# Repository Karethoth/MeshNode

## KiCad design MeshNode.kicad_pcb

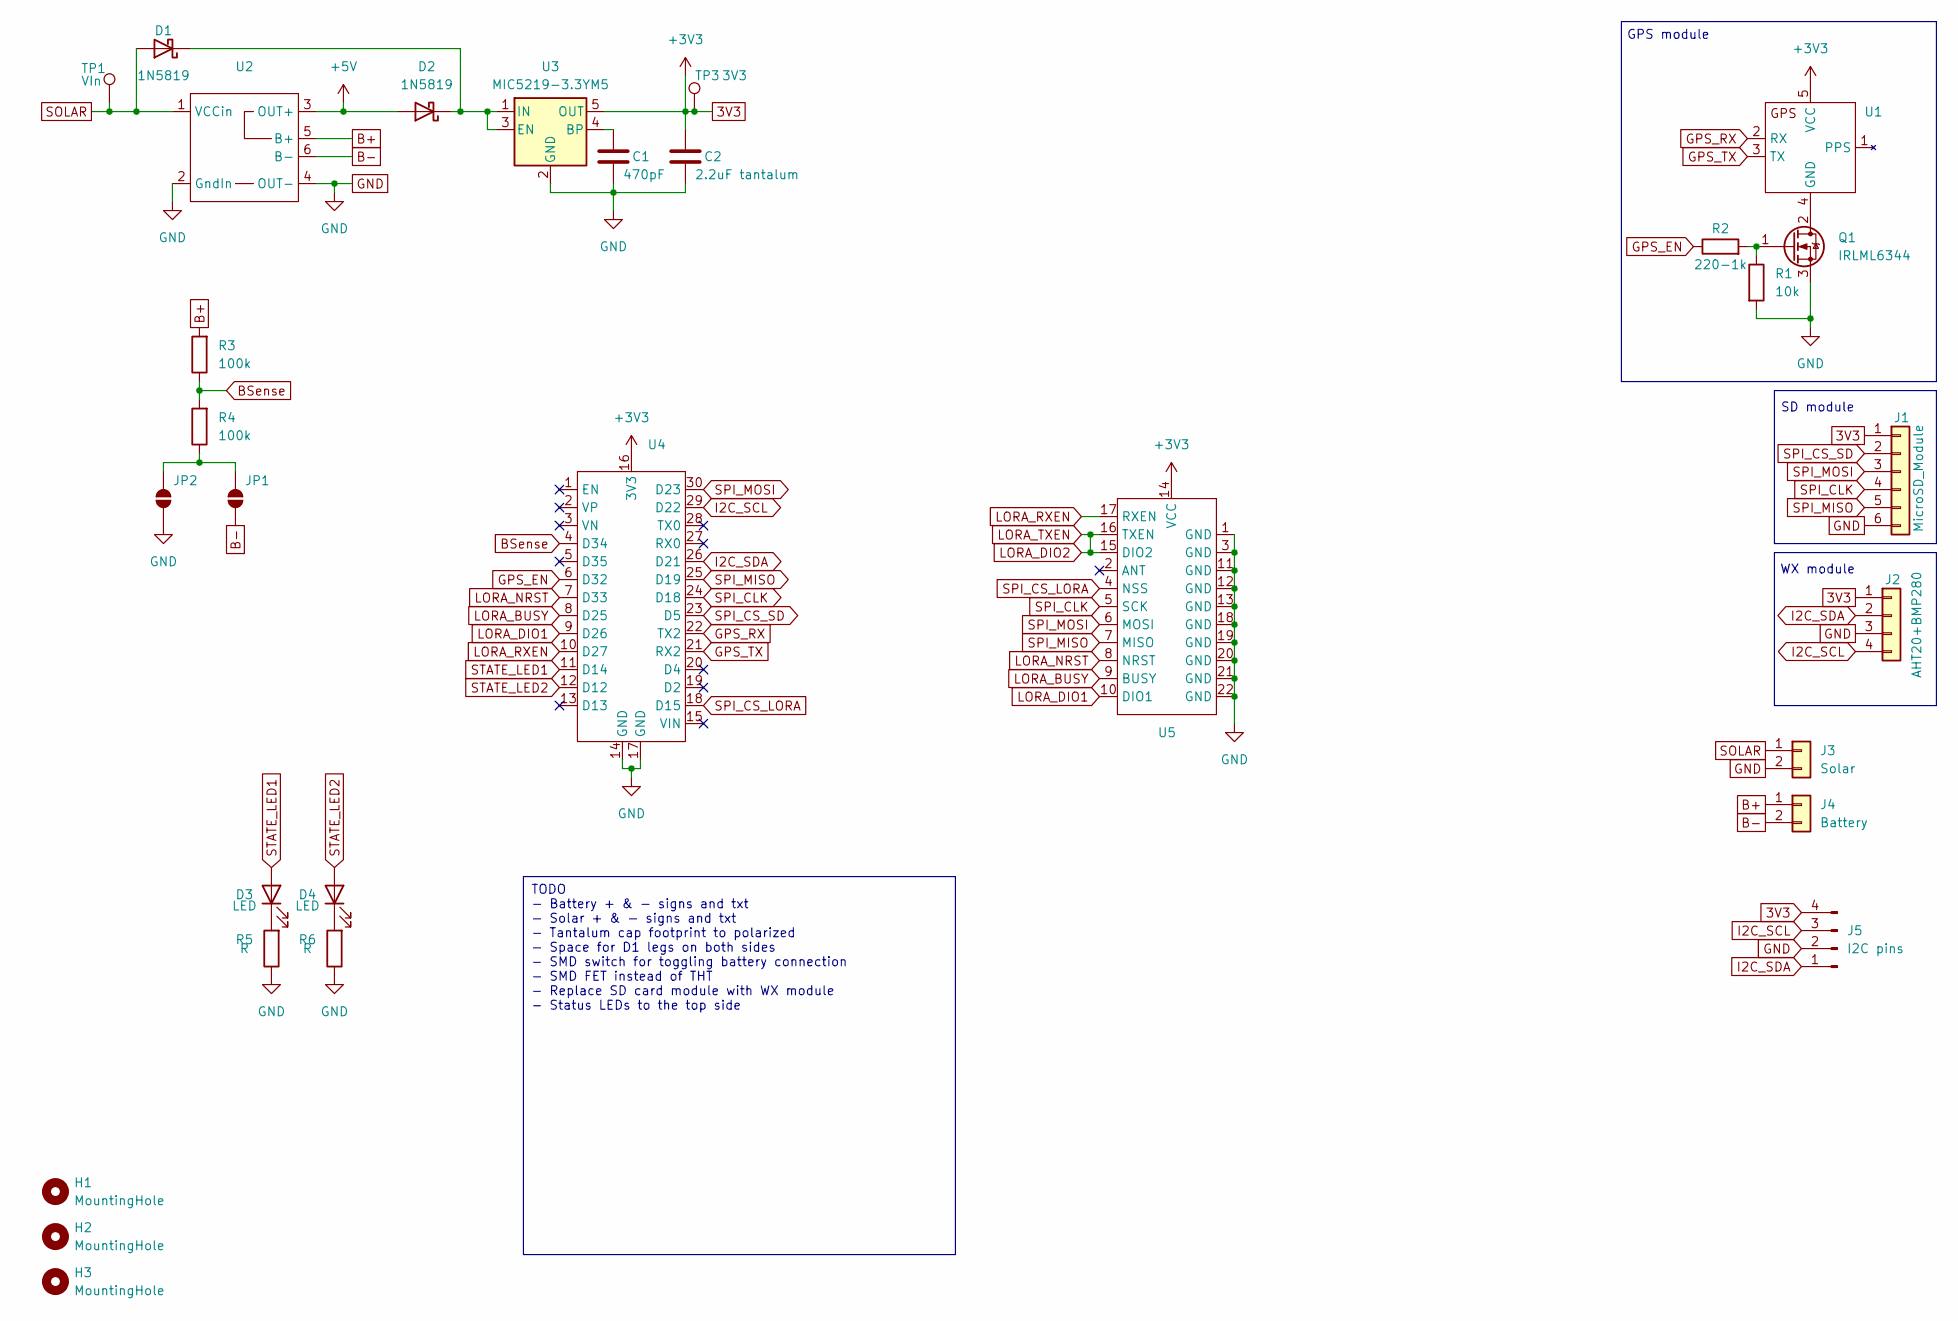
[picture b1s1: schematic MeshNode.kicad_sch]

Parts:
C1: 470pF; C_1206_3216Metric_Pad1.33x1.80mm_HandSolder
C2: 2.2uF tantalum; C_1206_3216Metric_Pad1.33x1.80mm_HandSolder
D1, D2: 1N5819; D_DO-41_SOD81_P10.16mm_Horizontal
D3, D4: LED; LED_0603_1608Metric_Pad1.05x0.95mm_HandSolder
H1, H2, H3: MountingHole; MountingHole_3mm
J1: MicroSD_Module
J2: AHT20+BMP280
J3: Solar; PinHeader_1x02_P2.54mm_Vertical
J4: Battery; PinHeader_1x02_P2.54mm_Vertical
J5: I2C pins; PinSocket_1x04_P2.54mm_Vertical
JP1, JP2: SolderJumper_2_Open; SolderJumper-2_P1.3mm_Open_RoundedPad1.0x1.5mm
Q1: IRLML6344; SOT-23
R1: 10k; R_0603_1608Metric
R2: 220-1k; R_0603_1608Metric
R3, R4: 100k; R_0603_1608Metric
R5, R6: R; R_0603_1608Metric_Pad0.98x0.95mm_HandSolder
TP1: VIn; TestPoint_Plated_Hole_D2.0mm
TP3: 3V3; TestPoint_Plated_Hole_D2.0mm
U1: GPS_Module
U2: TP4056
U3: MIC5219-3.3YM5; SOT-23-5
U4: WROOM32_Module
U5: EBYTE_900M22S

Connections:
3V3: C2.1, J1.1, J2.1, J5.4, TP3.1, U1.5 (VCC), U3.5 (OUT), U4.16 (3V3), U5.14 (VCC)
+5V: D2.2 (A), U2.3 (OUT+)
B+: J4.1, R3.2, U2.5 (B+)
B-: J4.2, JP1.2 (B), U2.6 (B-)
BSense: R3.1, R4.2, U4.4 (D34)
GND: C1.2, C2.2, J1.6, J2.3, J3.2, J5.2, JP2.1 (A), Q1.3 (S), R1.2, R5.1, R6.1, U2.2 (GndIn), U2.4 (OUT-), U3.2 (GND), U4.14 (GND), U4.17 (GND), U5.1 (GND), U5.3 (GND), U5.11 (GND), U5.12 (GND), U5.13 (GND), U5.18 (GND), U5.19 (GND), U5.20 (GND), U5.21 (GND), U5.22 (GND)
GPS_EN: R2.1, U4.6 (D32)
GPS_RX: U1.2 (RX), U4.22 (TX2)
GPS_TX: U1.3 (TX), U4.21 (RX2)
I2C_SCL: J2.4, J5.3, U4.29 (D22)
I2C_SDA: J2.2, J5.1, U4.26 (D21)
LORA_BUSY: U4.8 (D25), U5.9 (BUSY)
LORA_DIO1: U4.9 (D26), U5.10 (DIO1)
LORA_DIO2: U5.15 (DIO2), U5.16 (TXEN)
LORA_NRST: U4.7 (D33), U5.8 (NRST)
LORA_RXEN: U4.10 (D27), U5.17 (RXEN)
unnamed: D1.1 (K), D2.1 (K), U3.1 (IN), U3.3 (EN)
unnamed: D3.1 (K), R5.2
unnamed: D4.1 (K), R6.2
unnamed: JP1.1 (A), JP2.2 (B), R4.1
unnamed: Q1.2 (D), U1.4 (GND)
unnamed: Q1.1 (G), R1.1, R2.2
unnamed: C1.1, U3.4 (BP)
SOLAR: D1.2 (A), J3.1, TP1.1, U2.1 (VCCin)
SPI_CLK: J1.4, U4.24 (D18), U5.5 (SCK)
SPI_CS_LORA: U4.18 (D15), U5.4 (NSS)
SPI_CS_SD: J1.2, U4.23 (D5)
SPI_MISO: J1.5, U4.25 (D19), U5.7 (MISO)
SPI_MOSI: J1.3, U4.30 (D23), U5.6 (MOSI)
STATE_LED1: D3.2 (A), U4.11 (D14)
STATE_LED2: D4.2 (A), U4.12 (D12)

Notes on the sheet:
TODO - Battery + & - signs and txt - Solar + & - signs and txt - Tantalum cap footprint to polarized - Space for D1 legs on both sides - SMD switch for toggling battery connection - SMD FET instead of THT - Replace SD card module with WX module - Status LEDs to the top side
WX module
SD module
GPS module

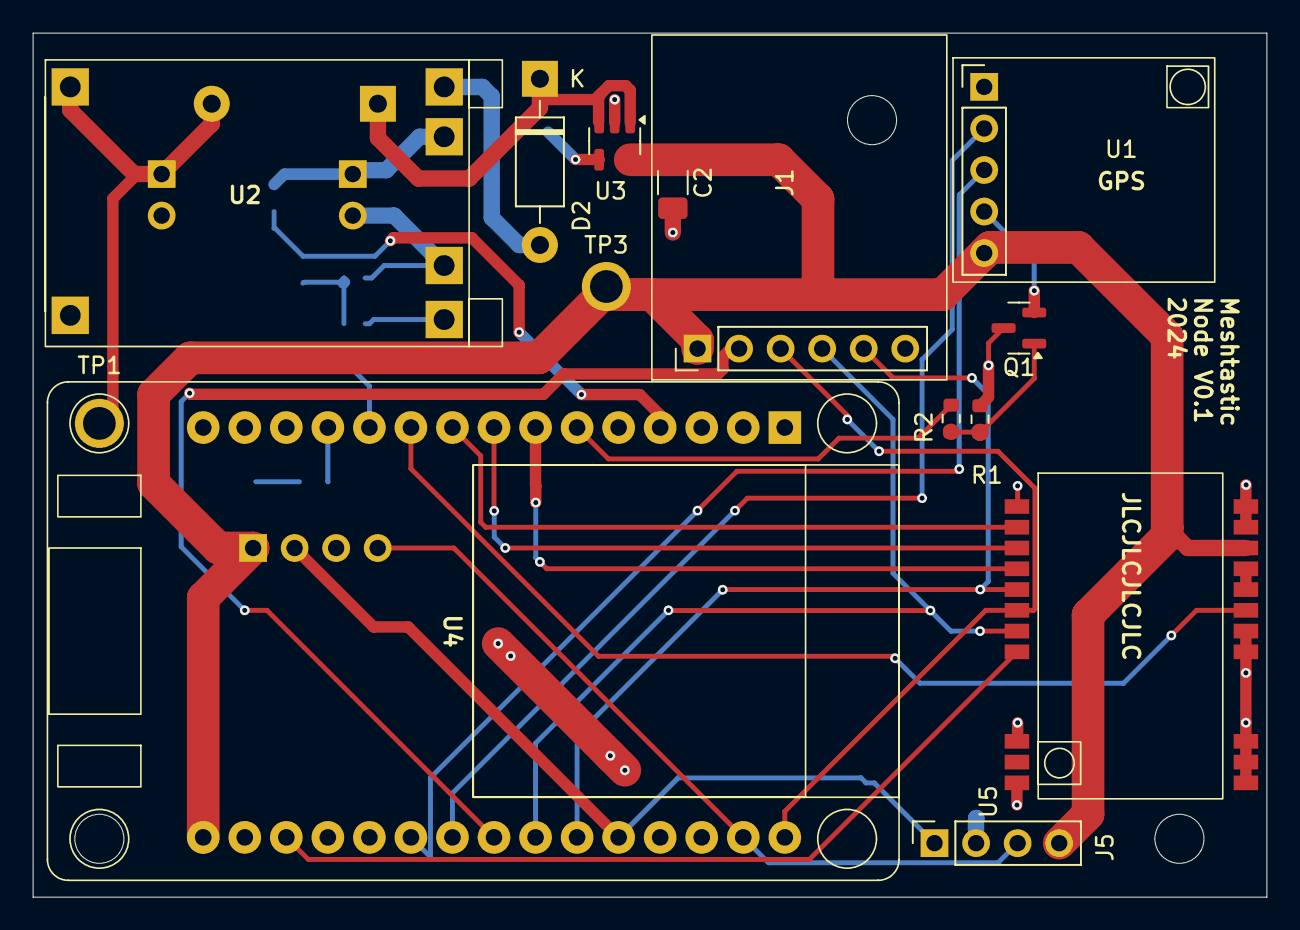
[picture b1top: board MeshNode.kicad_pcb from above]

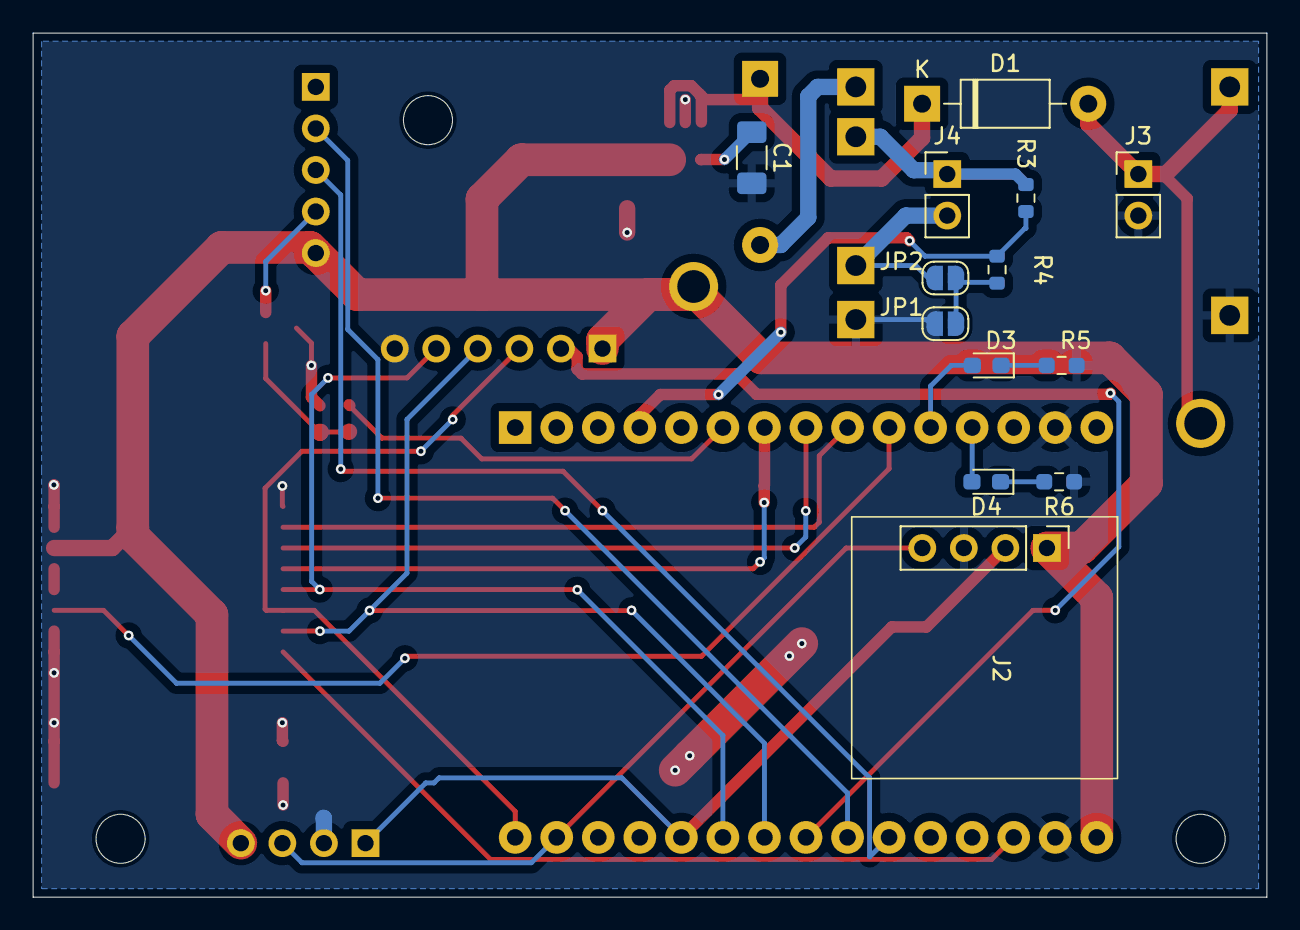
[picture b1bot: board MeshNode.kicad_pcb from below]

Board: 2 copper layers, 75.4 x 52.8 mm, 30 parts (13 on the bottom side), 31 nets.

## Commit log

2024-12-29 Initial commit V0.1
2024-12-29 Changed FET, resized traces, connected S22 connections
2024-12-29 Update TODO
